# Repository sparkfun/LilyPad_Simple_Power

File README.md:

LilyPad Simple Power
====================

[  
*LilyPad Simple Power (DEV-11893)*](https://www.sparkfun.com/products/11893)

This board provides a JST connector and an on/off switch, to enable your project with a power source and switching capabilities. 

Repository Contents
-------------------

* **/Hardware** - All Eagle design files (.brd, .sch)
* **/Production** - Test bed files and production panel files

Documentation
--------------
* **[Hookup Guide](https://learn.sparkfun.com/tutorials/lilypad-simple-power-hookup-guide)** - Basic hookup guide for the LilyPad Simple Power.

Product Versions
----------------
* [DEV-11893](https://www.sparkfun.com/products/11893 )- Version 2.1. 
* *[DEV-10085 (RETIRED)](https://www.sparkfun.com/products/retired/10085)- Version 1.4*

Version History
---------------
* [V_2.1](https://github.com/sparkfun/LilyPad_Simple_Power/tree/V_2.1) -GitHub files for version 2.1
* [V_2.0](https://github.com/sparkfun/LilyPad_Simple_Power/tree/V_2.0) -GitHub files for version 2.0
* [V_1.4](https://github.com/sparkfun/LilyPad_Simple_Power/tree/V_1.4) -GitHub files for version 1.4

License Information
-------------------
The hardware is released under [Creative Commons ShareAlike 4.0 International](https://creativecommons.org/licenses/by-sa/4.0/).

Distributed as-is; no warranty is given.

_**Note:** A portion of this sale is given back to Dr. Leah Buechley for continued development and education of e-textiles._

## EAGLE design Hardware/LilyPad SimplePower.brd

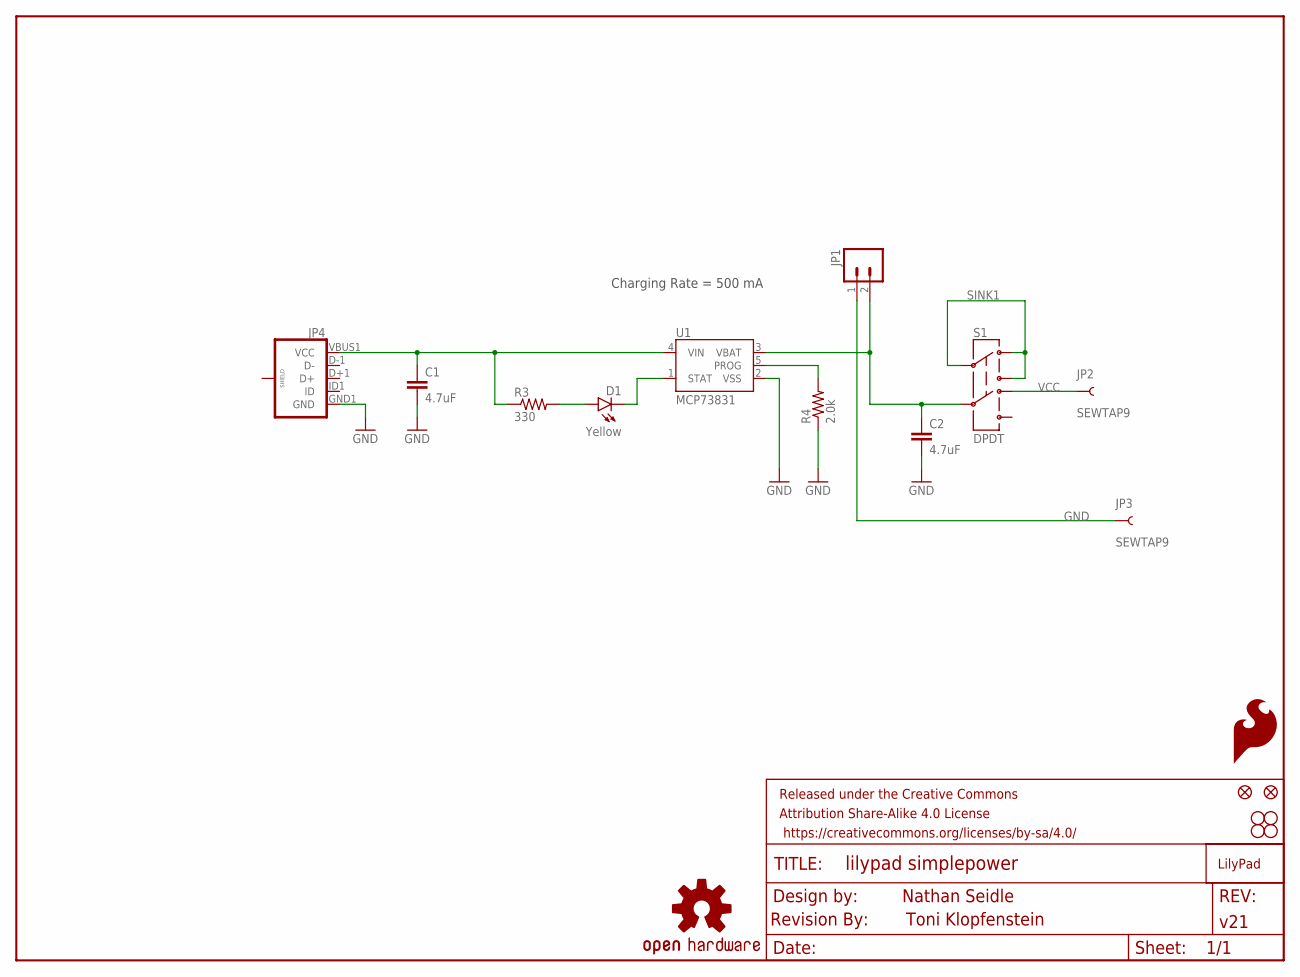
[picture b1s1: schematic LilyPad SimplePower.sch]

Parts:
C1, C2: 4.7uF; 0603-CAP
D1: Yellow; LED-0603
FID1, FID2: FIDUCIAL1X2; FIDUCIAL-1X2
FRAME1: FRAME-LETTER; CREATIVE_COMMONS
JP1: M02-JST-2MM-SMT; JST-2-SMD
JP2, JP3: SEWTAP9; PETAL-LONG-1-2SIDE
JP4: USB_MICROB_PLUGCONN-11752; USB-B-MICRO-SMD_V03
JP5: SFE_LOGO_FLAME.1_INCH; SFE_LOGO_FLAME_.1
R3: 330; 0603-RES
R4: 2.0k; 0603-RES
S1: DPDT; AYZ0202
STANDOFF1, STANDOFF2, STANDOFF3, STANDOFF4: SEW-HOLE-NO-PAD
U1: MCP73831; SOT23-5
U$1: LOGO-LPLP; LOGO-LILYPAD
U$5: OSHW-LOGOS; OSHW-LOGO-S
U$6: REVISION

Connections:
GND: C1.2, C2.2, JP1.1 (2), JP3.1, JP4.GND1 (GND), R4.1, U1.2 (VSS)
unnamed: C2.1, JP1.2 (1), S1.5, U1.3 (VBAT)
unnamed: C1.1, JP4.VBUS1 (VCC), R3.1, U1.4 (VIN)
unnamed: D1.C, U1.1 (STAT)
unnamed: D1.A, R3.2
unnamed: R4.2, U1.5 (PROG)
SINK1: S1.1, S1.2, S1.3
VCC: JP2.1, S1.4

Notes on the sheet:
Toni Klopfenstein
Charging Rate = 500 mA

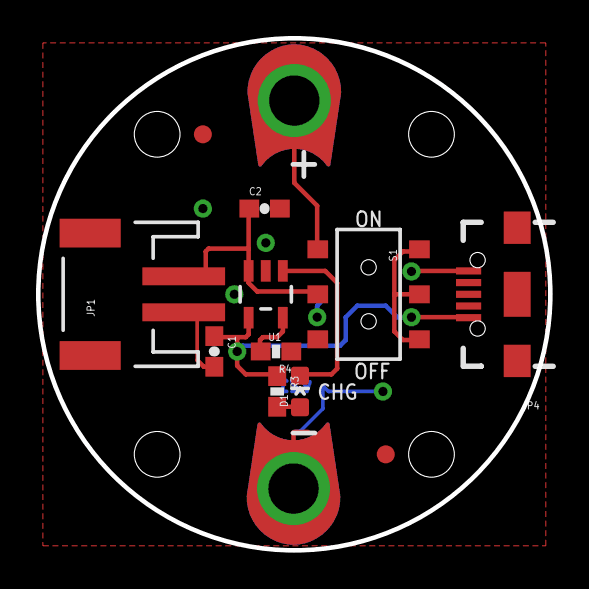
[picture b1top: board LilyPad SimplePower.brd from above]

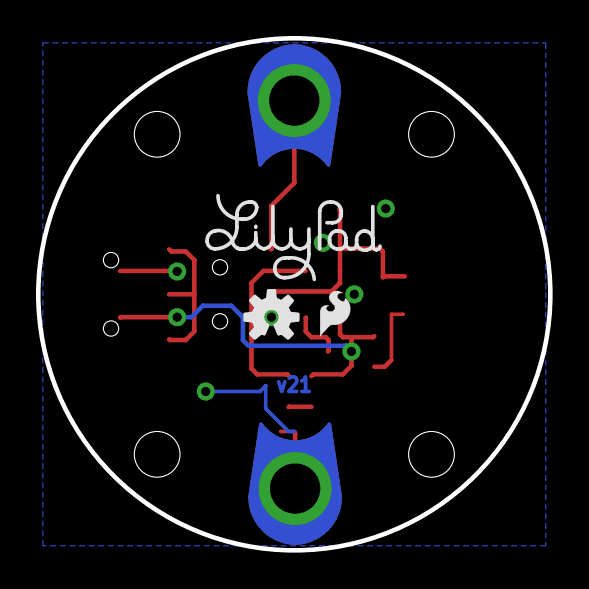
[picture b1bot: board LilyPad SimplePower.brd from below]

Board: 2 copper layers, 28.4 x 28.4 mm, 22 parts (3 on the bottom side), 8 nets.

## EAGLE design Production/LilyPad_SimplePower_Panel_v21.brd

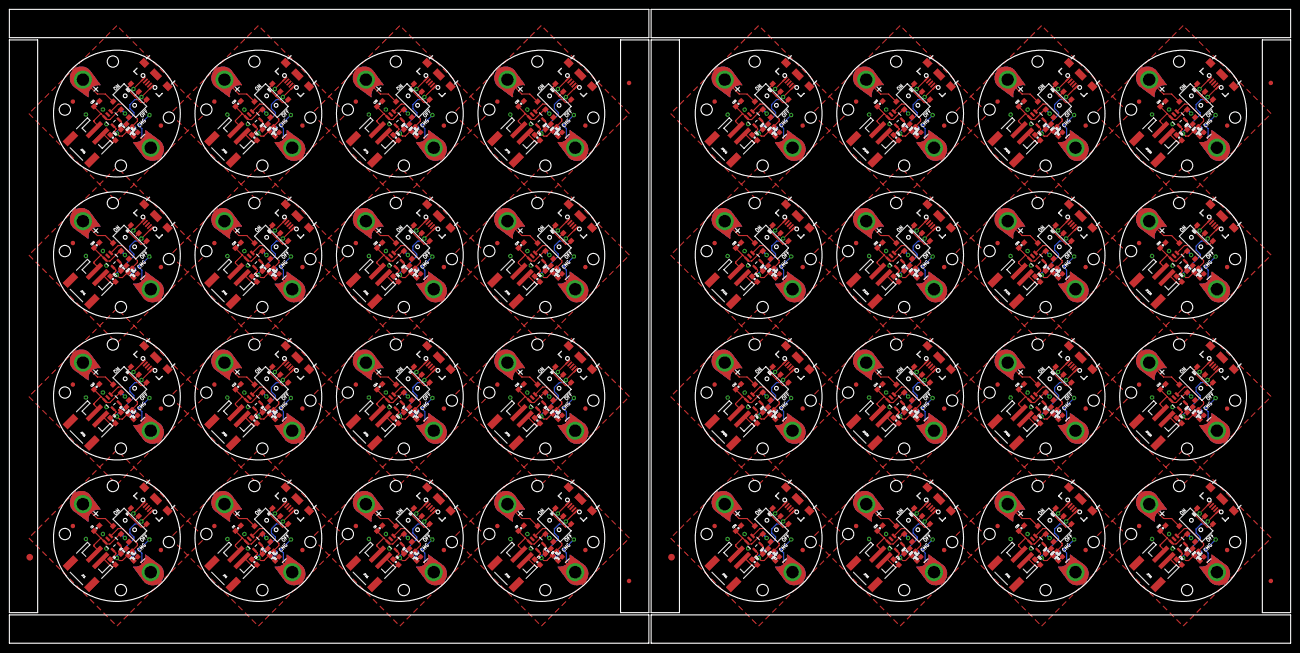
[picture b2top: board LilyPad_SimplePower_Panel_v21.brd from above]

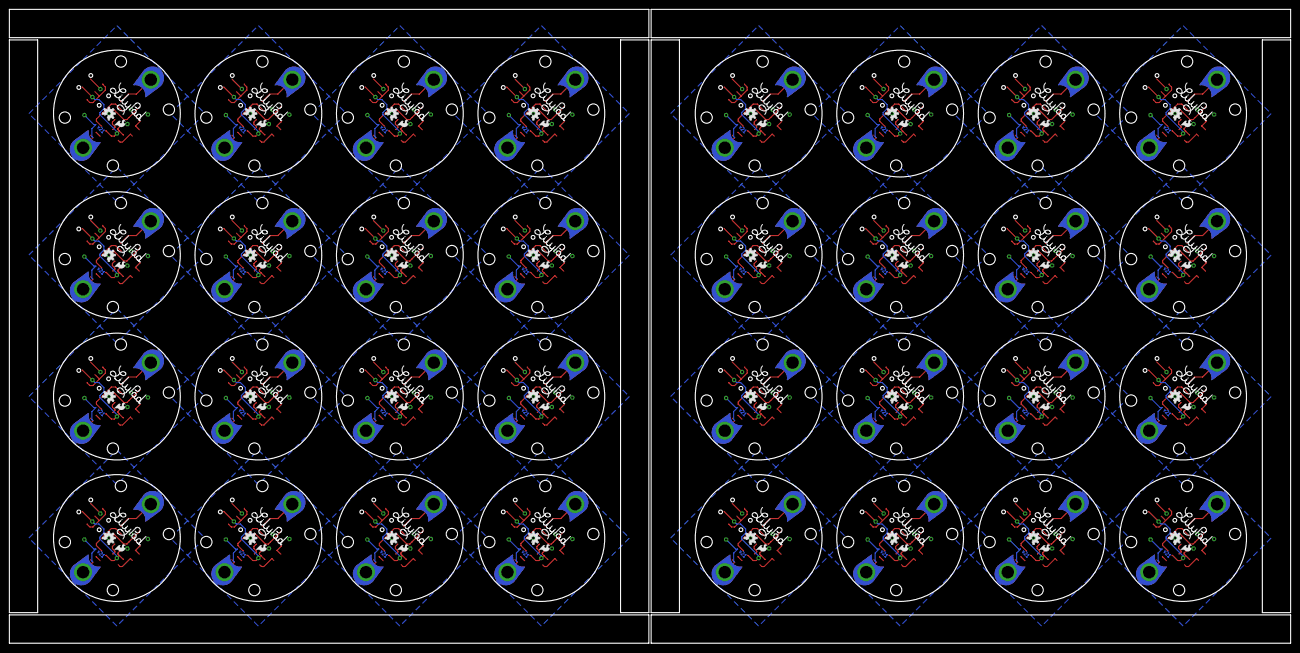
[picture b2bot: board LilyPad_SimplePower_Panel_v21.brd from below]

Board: 2 copper layers, 287.5 x 142.2 mm, 646 parts (96 on the bottom side), 256 nets.

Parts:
C1, C2, C3, C4, C5, C6, C7, C8, C9, C10, C11, C12, C13, C14, C15, C16, C17, C18, C19, C20, C21, C22, C23, C24, C25, C26, C27, C28, C29, C30, C31, C32, C33, C34, C35, C36, C37, C38, C39, C40, C41, C42, C43, C44, C45, C46, C47, C48, C49, C50, C51, C52, C53, C54, C55, C56, C57, C58, C59, C60, C61, C62, C63, C64: 4.7uF; 0603-CAP
D1, D2, D3, D4, D5, D6, D7, D8, D9, D10, D11, D12, D13, D14, D15, D16, D17, D18, D19, D20, D21, D22, D23, D24, D25, D26, D27, D28, D29, D30, D31, D32: Yellow; LED-0603
E$1, E$6: FIDUCIAL-1.5X3
E$2, E$3, E$4, E$5: FIDUCIAL-1X2
FID1, FID2, FID3, FID4, FID5, FID6, FID7, FID8, FID9, FID10, FID11, FID12, FID13, FID14, FID15, FID16, FID17, FID18, FID19, FID20, FID21, FID22, FID23, FID24, FID25, FID26, FID27, FID28, FID29, FID30, FID31, FID32, FID33, FID34, FID35, FID36, FID37, FID38, FID39, FID40, FID41, FID42, FID43, FID44, FID45, FID46, FID47, FID48, FID49, FID50, FID51, FID52, FID53, FID54, FID55, FID56, FID57, FID58, FID59, FID60, FID61, FID62, FID63, FID64: FIDUCIAL1X2; FIDUCIAL-1X2
JP1, JP6, JP11, JP16, JP21, JP26, JP31, JP36, JP41, JP46, JP51, JP56, JP61, JP66, JP71, JP76, JP81, JP86, JP91, JP96, JP101, JP106, JP111, JP116, JP121, JP126, JP131, JP136, JP141, JP146, JP151, JP156: M02-JST-2MM-SMT; JST-2-SMD
JP2, JP3, JP7, JP8, JP12, JP13, JP17, JP18, JP22, JP23, JP27, JP28, JP32, JP33, JP37, JP38, JP42, JP43, JP47, JP48, JP52, JP53, JP57, JP58, JP62, JP63, JP67, JP68, JP72, JP73, JP77, JP78, JP82, JP83, JP87, JP88, JP92, JP93, JP97, JP98, JP102, JP103, JP107, JP108, JP112, JP113, JP117, JP118, JP122, JP123, JP127, JP128, JP132, JP133, JP137, JP138, JP142, JP143, JP147, JP148, JP152, JP153, JP157, JP158: SEWTAP9; PETAL-LONG-1-2SIDE
JP4, JP10, JP15, JP20, JP25, JP30, JP35, JP40, JP45, JP50, JP55, JP60, JP65, JP70, JP75, JP80, JP85, JP90, JP95, JP100, JP105, JP110, JP115, JP120, JP125, JP130, JP135, JP140, JP145, JP150, JP155, JP160: USB_MICROB_PLUGCONN-11752; USB-B-MICRO-SMD_V03
JP5, JP9, JP14, JP19, JP24, JP29, JP34, JP39, JP44, JP49, JP54, JP59, JP64, JP69, JP74, JP79, JP84, JP89, JP94, JP99, JP104, JP109, JP114, JP119, JP124, JP129, JP134, JP139, JP144, JP149, JP154, JP159: SFE_LOGO_FLAME.1_INCH; SFE_LOGO_FLAME_.1
R1, R3, R5, R7, R9, R11, R13, R15, R17, R19, R21, R23, R25, R27, R29, R31, R33, R35, R37, R39, R41, R43, R45, R47, R49, R51, R53, R55, R57, R59, R61, R63: 330; 0603-RES
R2, R4, R6, R8, R10, R12, R14, R16, R18, R20, R22, R24, R26, R28, R30, R32, R34, R36, R38, R40, R42, R44, R46, R48, R50, R52, R54, R56, R58, R60, R62, R64: 2.0k; 0603-RES
S1, S2, S3, S4, S5, S6, S7, S8, S9, S10, S11, S12, S13, S14, S15, S16, S17, S18, S19, S20, S21, S22, S23, S24, S25, S26, S27, S28, S29, S30, S31, S32: DPDT; AYZ0202
STANDOFF1, STANDOFF2, STANDOFF3, STANDOFF4, STANDOFF5, STANDOFF6, STANDOFF7, STANDOFF8, STANDOFF9, STANDOFF10, STANDOFF11, STANDOFF12, STANDOFF13, STANDOFF14, STANDOFF15, STANDOFF16, STANDOFF17, STANDOFF18, STANDOFF19, STANDOFF20, STANDOFF21, STANDOFF22, STANDOFF23, STANDOFF24, STANDOFF25, STANDOFF26, STANDOFF27, STANDOFF28, STANDOFF29, STANDOFF30, STANDOFF31, STANDOFF32, STANDOFF33, STANDOFF34, STANDOFF35, STANDOFF36, STANDOFF37, STANDOFF38, STANDOFF39, STANDOFF40, STANDOFF41, STANDOFF42, STANDOFF43, STANDOFF44, STANDOFF45, STANDOFF46, STANDOFF47, STANDOFF48, STANDOFF49, STANDOFF50, STANDOFF51, STANDOFF52, STANDOFF53, STANDOFF54, STANDOFF55, STANDOFF56, STANDOFF57, STANDOFF58, STANDOFF59, STANDOFF60, STANDOFF61, STANDOFF62, STANDOFF63, STANDOFF64, STANDOFF65, STANDOFF66, STANDOFF67, STANDOFF68, STANDOFF69, STANDOFF70, STANDOFF71, STANDOFF72, STANDOFF73, STANDOFF74, STANDOFF75, STANDOFF76, STANDOFF77, STANDOFF78, STANDOFF79, STANDOFF80, STANDOFF81, STANDOFF82, STANDOFF83, STANDOFF84, STANDOFF85, STANDOFF86, STANDOFF87, STANDOFF88, STANDOFF89, STANDOFF90, STANDOFF91, STANDOFF92, STANDOFF93, STANDOFF94, STANDOFF95, STANDOFF96, STANDOFF97, STANDOFF98, STANDOFF99, STANDOFF100, STANDOFF101, STANDOFF102, STANDOFF103, STANDOFF104, STANDOFF105, STANDOFF106, STANDOFF107, STANDOFF108, STANDOFF109, STANDOFF110, STANDOFF111, STANDOFF112, STANDOFF113, STANDOFF114, STANDOFF115, STANDOFF116, STANDOFF117, STANDOFF118, STANDOFF119, STANDOFF120, STANDOFF121, STANDOFF122, STANDOFF123, STANDOFF124, STANDOFF125, STANDOFF126, STANDOFF127, STANDOFF128: SEW-HOLE-NO-PAD
U1, U2, U3, U4, U5, U6, U7, U8, U9, U10, U11, U12, U13, U14, U15, U16, U17, U18, U19, U20, U21, U22, U23, U24, U25, U26, U27, U28, U29, U30, U31, U32: MCP73831; SOT23-5
U$1, U$3, U$6, U$8, U$10, U$12, U$14, U$16, U$18, U$20, U$22, U$24, U$26, U$28, U$30, U$32, U$34, U$36, U$38, U$40, U$42, U$44, U$46, U$48, U$50, U$52, U$54, U$56, U$58, U$60, U$62, U$64: LOGO-LPLP; LOGO-LILYPAD
U$2, U$4, U$5, U$7, U$9, U$11, U$13, U$15, U$17, U$19, U$21, U$23, U$25, U$27, U$29, U$31, U$33, U$35, U$37, U$39, U$41, U$43, U$45, U$47, U$49, U$51, U$53, U$55, U$57, U$59, U$61, U$63: OSHW-LOGOS; OSHW-LOGO-S

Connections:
GND: C1.2, C2.2, JP1.1, JP3.1, JP4.GND1, R4.1, U1.2
GND1: C3.2, C4.2, JP6.1, JP7.1, JP10.GND1, R2.1, U2.2
GND2: C5.2, C6.2, JP11.1, JP12.1, JP15.GND1, R6.1, U3.2
GND3: C7.2, C8.2, JP16.1, JP17.1, JP20.GND1, R8.1, U4.2
GND4: C9.2, C10.2, JP21.1, JP22.1, JP25.GND1, R10.1, U5.2
GND5: C11.2, C12.2, JP26.1, JP27.1, JP30.GND1, R12.1, U6.2
GND6: C13.2, C14.2, JP31.1, JP32.1, JP35.GND1, R14.1, U7.2
GND7: C15.2, C16.2, JP36.1, JP37.1, JP40.GND1, R16.1, U8.2
GND8: C17.2, C18.2, JP41.1, JP42.1, JP45.GND1, R18.1, U9.2
GND9: C19.2, C20.2, JP46.1, JP47.1, JP50.GND1, R20.1, U10.2
GND10: C21.2, C22.2, JP51.1, JP52.1, JP55.GND1, R22.1, U11.2
GND11: C23.2, C24.2, JP56.1, JP57.1, JP60.GND1, R24.1, U12.2
GND12: C25.2, C26.2, JP61.1, JP62.1, JP65.GND1, R26.1, U13.2
GND13: C27.2, C28.2, JP66.1, JP67.1, JP70.GND1, R28.1, U14.2
GND14: C29.2, C30.2, JP71.1, JP72.1, JP75.GND1, R30.1, U15.2
GND15: C31.2, C32.2, JP76.1, JP77.1, JP80.GND1, R32.1, U16.2
GND16: C33.2, C34.2, JP81.1, JP82.1, JP85.GND1, R34.1, U17.2
GND17: C35.2, C36.2, JP86.1, JP87.1, JP90.GND1, R36.1, U18.2
GND18: C37.2, C38.2, JP91.1, JP92.1, JP95.GND1, R38.1, U19.2
GND19: C39.2, C40.2, JP96.1, JP97.1, JP100.GND1, R40.1, U20.2
GND20: C41.2, C42.2, JP101.1, JP102.1, JP105.GND1, R42.1, U21.2
GND21: C43.2, C44.2, JP106.1, JP107.1, JP110.GND1, R44.1, U22.2
GND22: C45.2, C46.2, JP111.1, JP112.1, JP115.GND1, R46.1, U23.2
GND23: C47.2, C48.2, JP116.1, JP117.1, JP120.GND1, R48.1, U24.2
GND24: C49.2, C50.2, JP121.1, JP122.1, JP125.GND1, R50.1, U25.2
GND25: C51.2, C52.2, JP126.1, JP127.1, JP130.GND1, R52.1, U26.2
GND26: C53.2, C54.2, JP131.1, JP132.1, JP135.GND1, R54.1, U27.2
GND27: C55.2, C56.2, JP136.1, JP137.1, JP140.GND1, R56.1, U28.2
GND28: C57.2, C58.2, JP141.1, JP142.1, JP145.GND1, R58.1, U29.2
GND29: C59.2, C60.2, JP146.1, JP147.1, JP150.GND1, R60.1, U30.2
GND30: C61.2, C62.2, JP151.1, JP152.1, JP155.GND1, R62.1, U31.2
GND31: C63.2, C64.2, JP156.1, JP157.1, JP160.GND1, R64.1, U32.2
unnamed: C2.1, JP1.2, S1.5, U1.3
unnamed: C4.1, JP6.2, S2.5, U2.3
unnamed: C1.1, JP4.VBUS1, R3.1, U1.4
unnamed: D1.C, U1.1
unnamed: D1.A, R3.2
unnamed: C3.1, JP10.VBUS1, R1.1, U2.4
unnamed: R4.2, U1.5
unnamed: D2.C, U2.1
unnamed: D2.A, R1.2
unnamed: R2.2, U2.5
unnamed: C6.1, JP11.2, S3.5, U3.3
unnamed: C5.1, JP15.VBUS1, R5.1, U3.4
unnamed: D3.C, U3.1
unnamed: D3.A, R5.2
unnamed: R6.2, U3.5
unnamed: C8.1, JP16.2, S4.5, U4.3
unnamed: C7.1, JP20.VBUS1, R7.1, U4.4
unnamed: D4.C, U4.1
unnamed: D4.A, R7.2
unnamed: R8.2, U4.5
unnamed: C10.1, JP21.2, S5.5, U5.3
unnamed: C9.1, JP25.VBUS1, R9.1, U5.4
unnamed: D5.C, U5.1
unnamed: D5.A, R9.2
unnamed: R10.2, U5.5
unnamed: C12.1, JP26.2, S6.5, U6.3
unnamed: C11.1, JP30.VBUS1, R11.1, U6.4
unnamed: D6.C, U6.1
unnamed: D6.A, R11.2
unnamed: R12.2, U6.5
unnamed: C14.1, JP31.2, S7.5, U7.3
unnamed: C13.1, JP35.VBUS1, R13.1, U7.4
unnamed: D7.C, U7.1
unnamed: D7.A, R13.2
unnamed: R14.2, U7.5
unnamed: C16.1, JP36.2, S8.5, U8.3
unnamed: C15.1, JP40.VBUS1, R15.1, U8.4
unnamed: D8.C, U8.1
unnamed: D8.A, R15.2
unnamed: R16.2, U8.5
unnamed: C18.1, JP41.2, S9.5, U9.3
unnamed: C17.1, JP45.VBUS1, R17.1, U9.4
unnamed: D9.C, U9.1
unnamed: D9.A, R17.2
unnamed: R18.2, U9.5
unnamed: C20.1, JP46.2, S10.5, U10.3
unnamed: C19.1, JP50.VBUS1, R19.1, U10.4
unnamed: D10.C, U10.1
unnamed: D10.A, R19.2
unnamed: R20.2, U10.5
unnamed: C22.1, JP51.2, S11.5, U11.3
unnamed: C21.1, JP55.VBUS1, R21.1, U11.4
unnamed: D11.C, U11.1
unnamed: D11.A, R21.2
unnamed: R22.2, U11.5
unnamed: C24.1, JP56.2, S12.5, U12.3
unnamed: C23.1, JP60.VBUS1, R23.1, U12.4
unnamed: D12.C, U12.1
unnamed: D12.A, R23.2
unnamed: R24.2, U12.5
unnamed: C26.1, JP61.2, S13.5, U13.3
unnamed: C25.1, JP65.VBUS1, R25.1, U13.4
unnamed: D13.C, U13.1
unnamed: D13.A, R25.2
unnamed: R26.2, U13.5
unnamed: C28.1, JP66.2, S14.5, U14.3
unnamed: C27.1, JP70.VBUS1, R27.1, U14.4
unnamed: D14.C, U14.1
unnamed: D14.A, R27.2
unnamed: R28.2, U14.5
unnamed: C30.1, JP71.2, S15.5, U15.3
unnamed: C29.1, JP75.VBUS1, R29.1, U15.4
unnamed: D15.C, U15.1
unnamed: D15.A, R29.2
unnamed: R30.2, U15.5
unnamed: C32.1, JP76.2, S16.5, U16.3
unnamed: C31.1, JP80.VBUS1, R31.1, U16.4
unnamed: D16.C, U16.1
unnamed: D16.A, R31.2
unnamed: R32.2, U16.5
unnamed: C34.1, JP81.2, S17.5, U17.3
unnamed: C33.1, JP85.VBUS1, R33.1, U17.4
unnamed: D17.C, U17.1
unnamed: D17.A, R33.2
unnamed: R34.2, U17.5
unnamed: C36.1, JP86.2, S18.5, U18.3
unnamed: C35.1, JP90.VBUS1, R35.1, U18.4
unnamed: D18.C, U18.1
unnamed: D18.A, R35.2
unnamed: R36.2, U18.5
unnamed: C38.1, JP91.2, S19.5, U19.3
unnamed: C37.1, JP95.VBUS1, R37.1, U19.4
unnamed: D19.C, U19.1
unnamed: D19.A, R37.2
unnamed: R38.2, U19.5
unnamed: C40.1, JP96.2, S20.5, U20.3
unnamed: C39.1, JP100.VBUS1, R39.1, U20.4
unnamed: D20.C, U20.1
unnamed: D20.A, R39.2
unnamed: R40.2, U20.5
unnamed: C42.1, JP101.2, S21.5, U21.3
unnamed: C41.1, JP105.VBUS1, R41.1, U21.4
unnamed: D21.C, U21.1
unnamed: D21.A, R41.2
unnamed: R42.2, U21.5
unnamed: C44.1, JP106.2, S22.5, U22.3
unnamed: C43.1, JP110.VBUS1, R43.1, U22.4
unnamed: D22.C, U22.1
unnamed: D22.A, R43.2
unnamed: R44.2, U22.5
unnamed: C46.1, JP111.2, S23.5, U23.3
unnamed: C45.1, JP115.VBUS1, R45.1, U23.4
unnamed: D23.C, U23.1
unnamed: D23.A, R45.2
unnamed: R46.2, U23.5
unnamed: C48.1, JP116.2, S24.5, U24.3
unnamed: C47.1, JP120.VBUS1, R47.1, U24.4
unnamed: D24.C, U24.1
unnamed: D24.A, R47.2
unnamed: R48.2, U24.5
unnamed: C50.1, JP121.2, S25.5, U25.3
unnamed: C49.1, JP125.VBUS1, R49.1, U25.4
unnamed: D25.C, U25.1
unnamed: D25.A, R49.2
unnamed: R50.2, U25.5
unnamed: C52.1, JP126.2, S26.5, U26.3
unnamed: C51.1, JP130.VBUS1, R51.1, U26.4
unnamed: D26.C, U26.1
unnamed: D26.A, R51.2
unnamed: R52.2, U26.5
unnamed: C54.1, JP131.2, S27.5, U27.3
unnamed: C53.1, JP135.VBUS1, R53.1, U27.4
unnamed: D27.C, U27.1
unnamed: D27.A, R53.2
unnamed: R54.2, U27.5
unnamed: C56.1, JP136.2, S28.5, U28.3
unnamed: C55.1, JP140.VBUS1, R55.1, U28.4
unnamed: D28.C, U28.1
unnamed: D28.A, R55.2
unnamed: R56.2, U28.5
unnamed: C58.1, JP141.2, S29.5, U29.3
unnamed: C57.1, JP145.VBUS1, R57.1, U29.4
unnamed: D29.C, U29.1
unnamed: D29.A, R57.2
unnamed: R58.2, U29.5
unnamed: C60.1, JP146.2, S30.5, U30.3
unnamed: C59.1, JP150.VBUS1, R59.1, U30.4
unnamed: D30.C, U30.1
unnamed: D30.A, R59.2
unnamed: R60.2, U30.5
unnamed: C62.1, JP151.2, S31.5, U31.3
unnamed: C61.1, JP155.VBUS1, R61.1, U31.4
unnamed: D31.C, U31.1
unnamed: D31.A, R61.2
unnamed: R62.2, U31.5
unnamed: C64.1, JP156.2, S32.5, U32.3
unnamed: C63.1, JP160.VBUS1, R63.1, U32.4
unnamed: D32.C, U32.1
unnamed: D32.A, R63.2
unnamed: R64.2, U32.5
SINK1: S1.1, S1.2, S1.3
SINK2: S2.1, S2.2, S2.3
SINK3: S3.1, S3.2, S3.3
SINK4: S4.1, S4.2, S4.3
SINK5: S5.1, S5.2, S5.3
SINK6: S6.1, S6.2, S6.3
SINK7: S7.1, S7.2, S7.3
SINK8: S8.1, S8.2, S8.3
SINK9: S9.1, S9.2, S9.3
SINK10: S10.1, S10.2, S10.3
SINK11: S11.1, S11.2, S11.3
SINK12: S12.1, S12.2, S12.3
SINK13: S13.1, S13.2, S13.3
SINK14: S14.1, S14.2, S14.3
SINK15: S15.1, S15.2, S15.3
SINK16: S16.1, S16.2, S16.3
SINK17: S17.1, S17.2, S17.3
SINK18: S18.1, S18.2, S18.3
SINK19: S19.1, S19.2, S19.3
SINK20: S20.1, S20.2, S20.3
SINK21: S21.1, S21.2, S21.3
SINK22: S22.1, S22.2, S22.3
SINK23: S23.1, S23.2, S23.3
SINK24: S24.1, S24.2, S24.3
SINK25: S25.1, S25.2, S25.3
SINK26: S26.1, S26.2, S26.3
SINK27: S27.1, S27.2, S27.3
SINK28: S28.1, S28.2, S28.3
SINK29: S29.1, S29.2, S29.3
SINK30: S30.1, S30.2, S30.3
SINK31: S31.1, S31.2, S31.3
SINK32: S32.1, S32.2, S32.3
VCC: JP2.1, S1.4
VCC1: JP8.1, S2.4
VCC2: JP13.1, S3.4
VCC3: JP18.1, S4.4
VCC4: JP23.1, S5.4
VCC5: JP28.1, S6.4
VCC6: JP33.1, S7.4
VCC7: JP38.1, S8.4
VCC8: JP43.1, S9.4
VCC9: JP48.1, S10.4
VCC10: JP53.1, S11.4
VCC11: JP58.1, S12.4
VCC12: JP63.1, S13.4
VCC13: JP68.1, S14.4
VCC14: JP73.1, S15.4
VCC15: JP78.1, S16.4
VCC16: JP83.1, S17.4
VCC17: JP88.1, S18.4
VCC18: JP93.1, S19.4
VCC19: JP98.1, S20.4
VCC20: JP103.1, S21.4
VCC21: JP108.1, S22.4
VCC22: JP113.1, S23.4
VCC23: JP118.1, S24.4
VCC24: JP123.1, S25.4
VCC25: JP128.1, S26.4
VCC26: JP133.1, S27.4
VCC27: JP138.1, S28.4
VCC28: JP143.1, S29.4
VCC29: JP148.1, S30.4
VCC30: JP153.1, S31.4
VCC31: JP158.1, S32.4

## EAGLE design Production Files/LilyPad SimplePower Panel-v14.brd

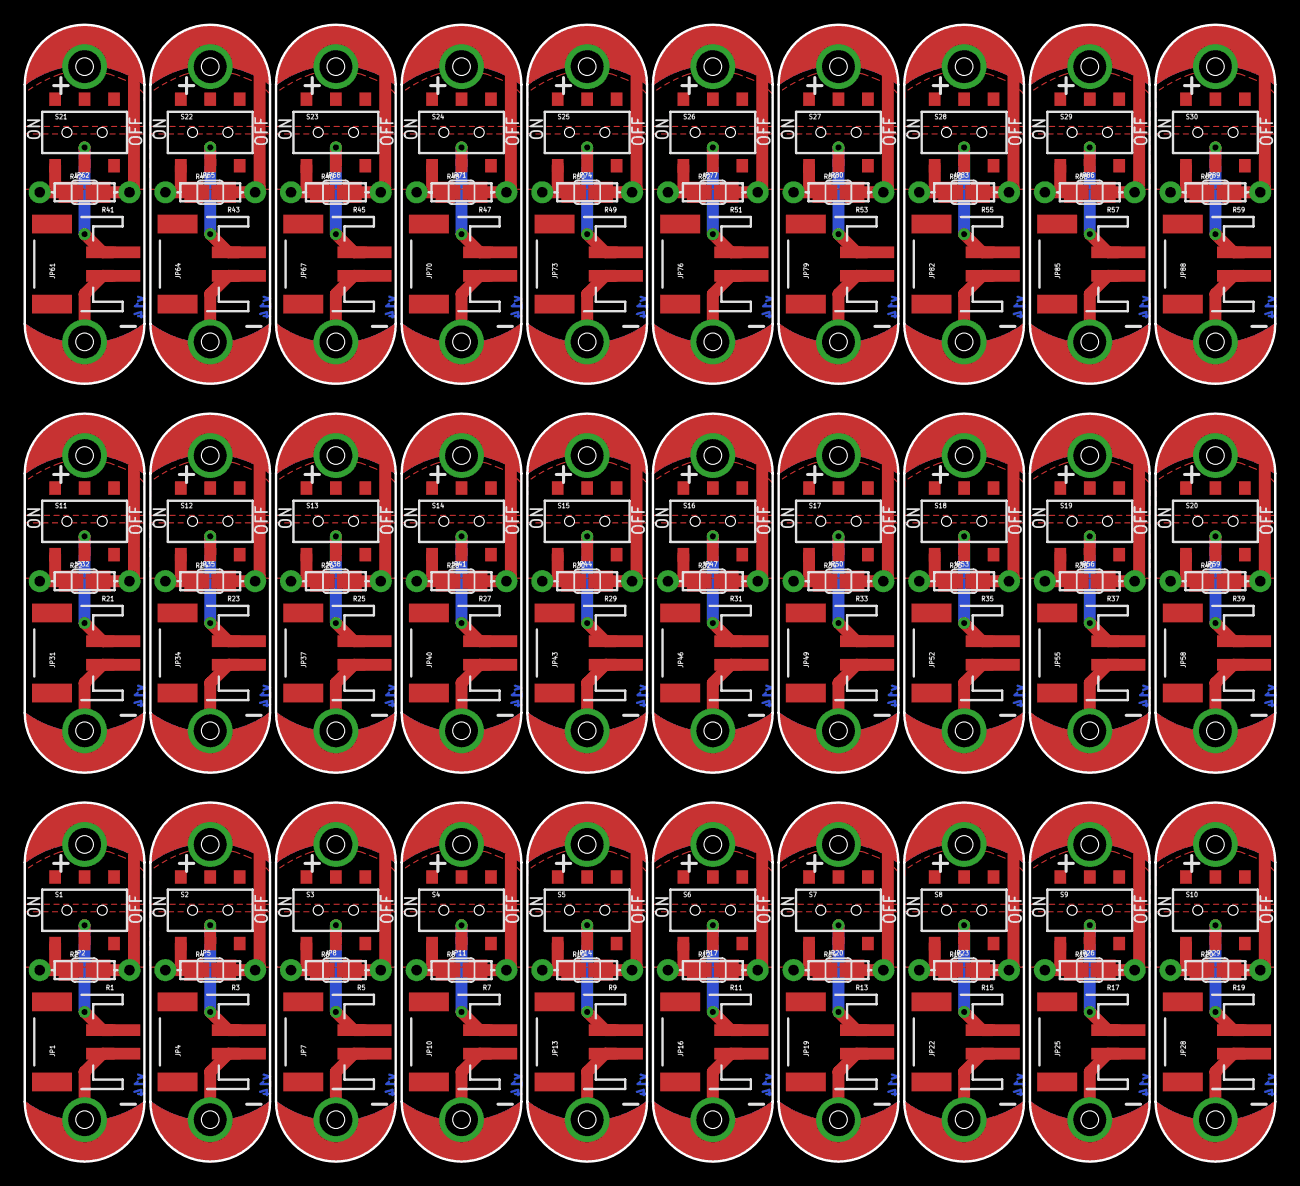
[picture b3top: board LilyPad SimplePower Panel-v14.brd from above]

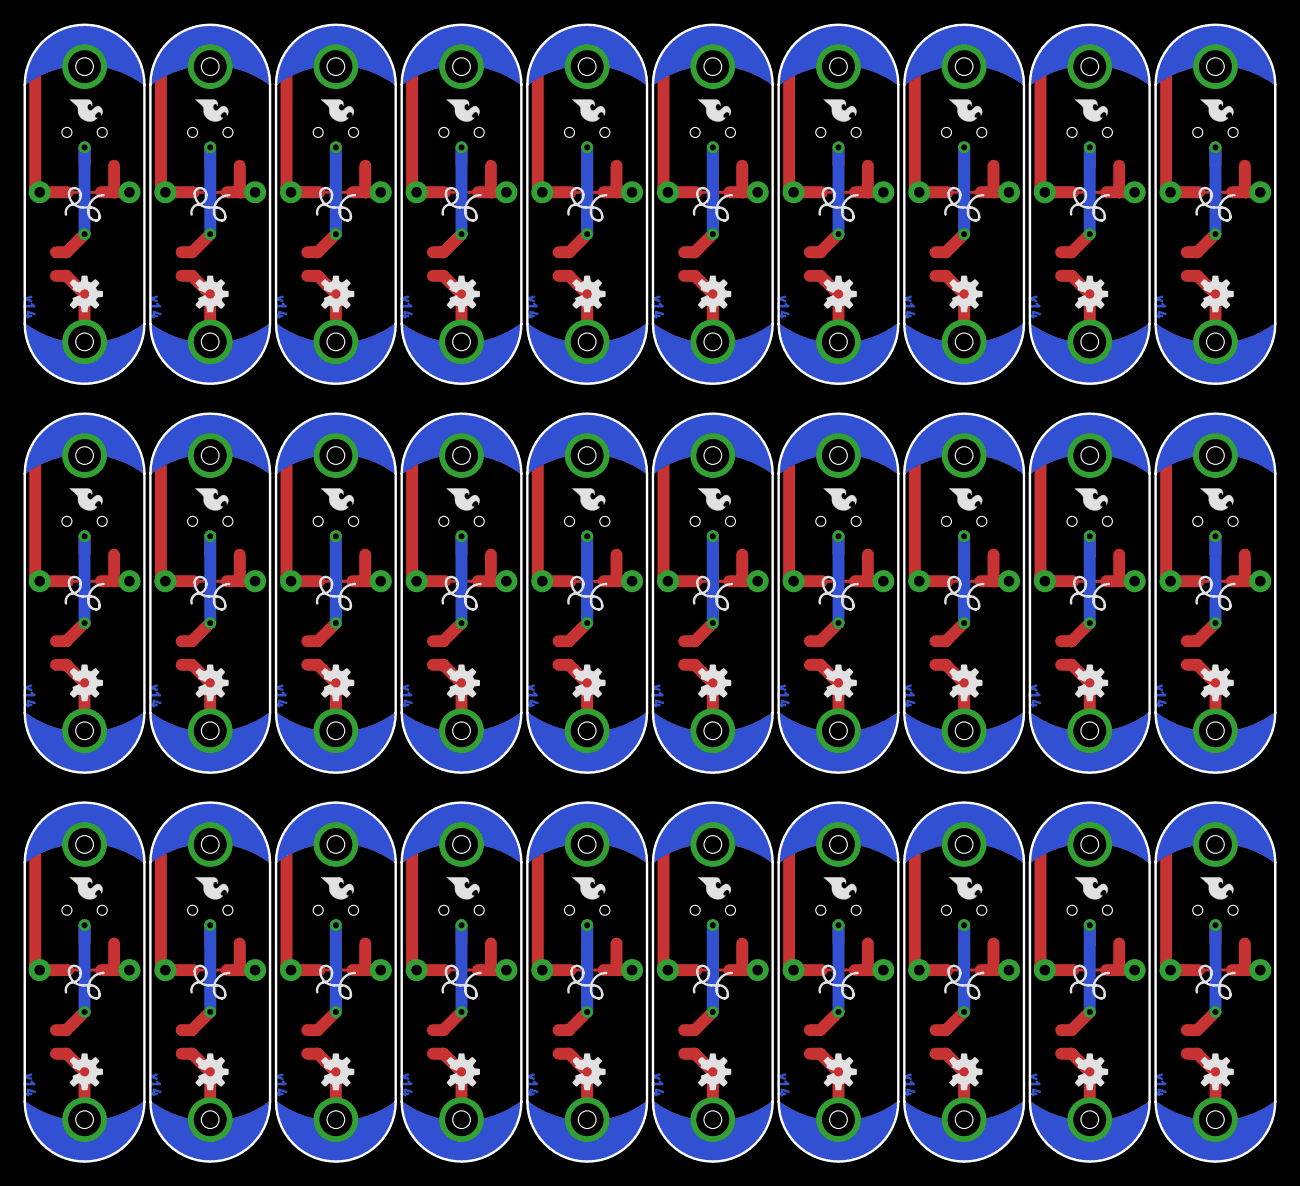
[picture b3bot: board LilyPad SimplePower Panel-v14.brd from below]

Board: 2 copper layers, 106.2 x 96.5 mm, 300 parts (90 on the bottom side), 150 nets.

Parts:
JP1, JP4, JP7, JP10, JP13, JP16, JP19, JP22, JP25, JP28, JP31, JP34, JP37, JP40, JP43, JP46, JP49, JP52, JP55, JP58, JP61, JP64, JP67, JP70, JP73, JP76, JP79, JP82, JP85, JP88: JST-2-SMD
JP2, JP5, JP8, JP11, JP14, JP17, JP20, JP23, JP26, JP29, JP32, JP35, JP38, JP41, JP44, JP47, JP50, JP53, JP56, JP59, JP62, JP65, JP68, JP71, JP74, JP77, JP80, JP83, JP86, JP89: SJ_2S
JP3, JP6, JP9, JP12, JP15, JP18, JP21, JP24, JP27, JP30, JP33, JP36, JP39, JP42, JP45, JP48, JP51, JP54, JP57, JP60, JP63, JP66, JP69, JP72, JP75, JP78, JP81, JP84, JP87, JP90: LOGO-SFESK; SFE-LOGO-FLAME
R1, R3, R5, R7, R9, R11, R13, R15, R17, R19, R21, R23, R25, R27, R29, R31, R33, R35, R37, R39, R41, R43, R45, R47, R49, R51, R53, R55, R57, R59: AXIAL-0.3
R2, R4, R6, R8, R10, R12, R14, R16, R18, R20, R22, R24, R26, R28, R30, R32, R34, R36, R38, R40, R42, R44, R46, R48, R50, R52, R54, R56, R58, R60: 1206
S1, S2, S3, S4, S5, S6, S7, S8, S9, S10, S11, S12, S13, S14, S15, S16, S17, S18, S19, S20, S21, S22, S23, S24, S25, S26, S27, S28, S29, S30: Power; AYZ0202
U$1, U$7, U$11, U$15, U$19, U$23, U$27, U$31, U$35, U$39, U$43, U$47, U$51, U$55, U$59, U$63, U$67, U$71, U$75, U$79, U$83, U$87, U$91, U$95, U$99, U$103, U$107, U$111, U$115, U$119: LOGO-LPL; LOGO-L
U$2, U$3, U$4, U$6, U$9, U$10, U$13, U$14, U$17, U$18, U$21, U$22, U$25, U$26, U$29, U$30, U$33, U$34, U$37, U$38, U$41, U$42, U$45, U$46, U$49, U$50, U$53, U$54, U$57, U$58, U$61, U$62, U$65, U$66, U$69, U$70, U$73, U$74, U$77, U$78, U$81, U$82, U$85, U$86, U$89, U$90, U$93, U$94, U$97, U$98, U$101, U$102, U$105, U$106, U$109, U$110, U$113, U$114, U$117, U$118: SEWTAP7; PETAL-LARGE-2SIDE
U$5, U$8, U$12, U$16, U$20, U$24, U$28, U$32, U$36, U$40, U$44, U$48, U$52, U$56, U$60, U$64, U$68, U$72, U$76, U$80, U$84, U$88, U$92, U$96, U$100, U$104, U$108, U$112, U$116, U$120: OSHW-LOGOS; OSHW-LOGO-S

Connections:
+: JP2.2, R1.P$1, R2.2, U$4.1
+1: JP5.2, R3.P$1, R4.2, U$6.1
+2: JP8.2, R5.P$1, R6.2, U$10.1
+3: JP11.2, R7.P$1, R8.2, U$14.1
+4: JP14.2, R9.P$1, R10.2, U$18.1
+5: JP17.2, R11.P$1, R12.2, U$22.1
+6: JP20.2, R13.P$1, R14.2, U$26.1
+7: JP23.2, R15.P$1, R16.2, U$30.1
+8: JP26.2, R17.P$1, R18.2, U$34.1
+9: JP29.2, R19.P$1, R20.2, U$38.1
+10: JP32.2, R21.P$1, R22.2, U$42.1
+11: JP35.2, R23.P$1, R24.2, U$46.1
+12: JP38.2, R25.P$1, R26.2, U$50.1
+13: JP41.2, R27.P$1, R28.2, U$54.1
+14: JP44.2, R29.P$1, R30.2, U$58.1
+15: JP47.2, R31.P$1, R32.2, U$62.1
+16: JP50.2, R33.P$1, R34.2, U$66.1
+17: JP53.2, R35.P$1, R36.2, U$70.1
+18: JP56.2, R37.P$1, R38.2, U$74.1
+19: JP59.2, R39.P$1, R40.2, U$78.1
+20: JP62.2, R41.P$1, R42.2, U$82.1
+21: JP65.2, R43.P$1, R44.2, U$86.1
+22: JP68.2, R45.P$1, R46.2, U$90.1
+23: JP71.2, R47.P$1, R48.2, U$94.1
+24: JP74.2, R49.P$1, R50.2, U$98.1
+25: JP77.2, R51.P$1, R52.2, U$102.1
+26: JP80.2, R53.P$1, R54.2, U$106.1
+27: JP83.2, R55.P$1, R56.2, U$110.1
+28: JP86.2, R57.P$1, R58.2, U$114.1
+29: JP89.2, R59.P$1, R60.2, U$118.1
GND: JP1.1, U$3.1
GND1: JP4.1, U$2.1
GND2: JP7.1, U$9.1
GND3: JP10.1, U$13.1
GND4: JP13.1, U$17.1
GND5: JP16.1, U$21.1
GND6: JP19.1, U$25.1
GND7: JP22.1, U$29.1
GND8: JP25.1, U$33.1
GND9: JP28.1, U$37.1
GND10: JP31.1, U$41.1
GND11: JP34.1, U$45.1
GND12: JP37.1, U$49.1
GND13: JP40.1, U$53.1
GND14: JP43.1, U$57.1
GND15: JP46.1, U$61.1
GND16: JP49.1, U$65.1
GND17: JP52.1, U$69.1
GND18: JP55.1, U$73.1
GND19: JP58.1, U$77.1
GND20: JP61.1, U$81.1
GND21: JP64.1, U$85.1
GND22: JP67.1, U$89.1
GND23: JP70.1, U$93.1
GND24: JP73.1, U$97.1
GND25: JP76.1, U$101.1
GND26: JP79.1, U$105.1
GND27: JP82.1, U$109.1
GND28: JP85.1, U$113.1
GND29: JP88.1, U$117.1
unnamed: JP1.2, S1.5
unnamed: JP2.1, R1.P$2, R2.1, S1.4
unnamed: JP5.1, R3.P$2, R4.1, S2.4
unnamed: JP4.2, S2.5
unnamed: JP8.1, R5.P$2, R6.1, S3.4
unnamed: JP7.2, S3.5
unnamed: JP11.1, R7.P$2, R8.1, S4.4
unnamed: JP10.2, S4.5
unnamed: JP14.1, R9.P$2, R10.1, S5.4
unnamed: JP13.2, S5.5
unnamed: JP17.1, R11.P$2, R12.1, S6.4
unnamed: JP16.2, S6.5
unnamed: JP20.1, R13.P$2, R14.1, S7.4
unnamed: JP19.2, S7.5
unnamed: JP23.1, R15.P$2, R16.1, S8.4
unnamed: JP22.2, S8.5
unnamed: JP26.1, R17.P$2, R18.1, S9.4
unnamed: JP25.2, S9.5
unnamed: JP29.1, R19.P$2, R20.1, S10.4
unnamed: JP28.2, S10.5
unnamed: JP32.1, R21.P$2, R22.1, S11.4
unnamed: JP31.2, S11.5
unnamed: JP35.1, R23.P$2, R24.1, S12.4
unnamed: JP34.2, S12.5
unnamed: JP38.1, R25.P$2, R26.1, S13.4
unnamed: JP37.2, S13.5
unnamed: JP41.1, R27.P$2, R28.1, S14.4
unnamed: JP40.2, S14.5
unnamed: JP44.1, R29.P$2, R30.1, S15.4
unnamed: JP43.2, S15.5
unnamed: JP47.1, R31.P$2, R32.1, S16.4
unnamed: JP46.2, S16.5
unnamed: JP50.1, R33.P$2, R34.1, S17.4
unnamed: JP49.2, S17.5
unnamed: JP53.1, R35.P$2, R36.1, S18.4
unnamed: JP52.2, S18.5
unnamed: JP56.1, R37.P$2, R38.1, S19.4
unnamed: JP55.2, S19.5
unnamed: JP59.1, R39.P$2, R40.1, S20.4
unnamed: JP58.2, S20.5
unnamed: JP62.1, R41.P$2, R42.1, S21.4
unnamed: JP61.2, S21.5
unnamed: JP65.1, R43.P$2, R44.1, S22.4
unnamed: JP64.2, S22.5
unnamed: JP68.1, R45.P$2, R46.1, S23.4
unnamed: JP67.2, S23.5
unnamed: JP71.1, R47.P$2, R48.1, S24.4
unnamed: JP70.2, S24.5
unnamed: JP74.1, R49.P$2, R50.1, S25.4
unnamed: JP73.2, S25.5
unnamed: JP77.1, R51.P$2, R52.1, S26.4
unnamed: JP76.2, S26.5
unnamed: JP80.1, R53.P$2, R54.1, S27.4
unnamed: JP79.2, S27.5
unnamed: JP83.1, R55.P$2, R56.1, S28.4
unnamed: JP82.2, S28.5
unnamed: JP86.1, R57.P$2, R58.1, S29.4
unnamed: JP85.2, S29.5
unnamed: JP89.1, R59.P$2, R60.1, S30.4
unnamed: JP88.2, S30.5
SINK1: S1.1, S1.2, S1.3
SINK3: S2.1, S2.2, S2.3
SINK5: S3.1, S3.2, S3.3
SINK7: S4.1, S4.2, S4.3
SINK9: S5.1, S5.2, S5.3
SINK11: S6.1, S6.2, S6.3
SINK13: S7.1, S7.2, S7.3
SINK15: S8.1, S8.2, S8.3
SINK17: S9.1, S9.2, S9.3
SINK19: S10.1, S10.2, S10.3
SINK21: S11.1, S11.2, S11.3
SINK23: S12.1, S12.2, S12.3
SINK25: S13.1, S13.2, S13.3
SINK27: S14.1, S14.2, S14.3
SINK29: S15.1, S15.2, S15.3
SINK31: S16.1, S16.2, S16.3
SINK33: S17.1, S17.2, S17.3
SINK35: S18.1, S18.2, S18.3
SINK37: S19.1, S19.2, S19.3
SINK39: S20.1, S20.2, S20.3
SINK41: S21.1, S21.2, S21.3
SINK43: S22.1, S22.2, S22.3
SINK45: S23.1, S23.2, S23.3
SINK47: S24.1, S24.2, S24.3
SINK49: S25.1, S25.2, S25.3
SINK51: S26.1, S26.2, S26.3
SINK53: S27.1, S27.2, S27.3
SINK55: S28.1, S28.2, S28.3
SINK57: S29.1, S29.2, S29.3
SINK59: S30.1, S30.2, S30.3

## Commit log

2013-05-13 Initial file commit
2013-06-06 V14 Production Readied
    Created Panel
2014-01-21 Hardware Version 2.0 commit
2014-01-21 Saving board file again
2014-01-29 Adding review changes
2014-02-04 deleted old v14 panel
2014-02-17 Fixing PWR label to CHG on LED
2014-04-03 midway work on updating design
2014-04-03 More petal work
2014-05-12 Initial polygon pours corrected
2014-05-13 Updating bRestrict to give Lilypad petal pattern
2014-05-14 Updating minor fixes for acid traps
2014-08-12 Updating board with more classic LilyPad design
2014-09-02 Updating round two protos again to fix missing drill hits.
2014-10-20 Cleaning up schematic layout
2014-10-27 added board fiducials
2014-10-27 Hardware files turned 45 degrees for improved panelization
2014-10-27 Updating polygon to GND layer
2014-10-27 created v20 panel
2015-01-15 Updating README with new product links
2015-01-29 Fixing short, updating parts to match QC checklist
2015-02-03 Fixing QC issues
2015-02-04 first push of panel creation
2015-02-04 Rotating board 45 degrees for panelization
2015-02-05 Created panel v21
2015-05-13 Updating README, fixing file names

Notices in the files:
parts and their libraries:
SparkFun-Aesthetics: Licensing: CC v3.0 Share-Alike You are welcome to use this library for commercial purposes.
SparkFun-Aesthetics: Released under the Creative Commons Attribution Share-Alike 4.0 License
SparkFun-Aesthetics: Released under the Creative Commons
